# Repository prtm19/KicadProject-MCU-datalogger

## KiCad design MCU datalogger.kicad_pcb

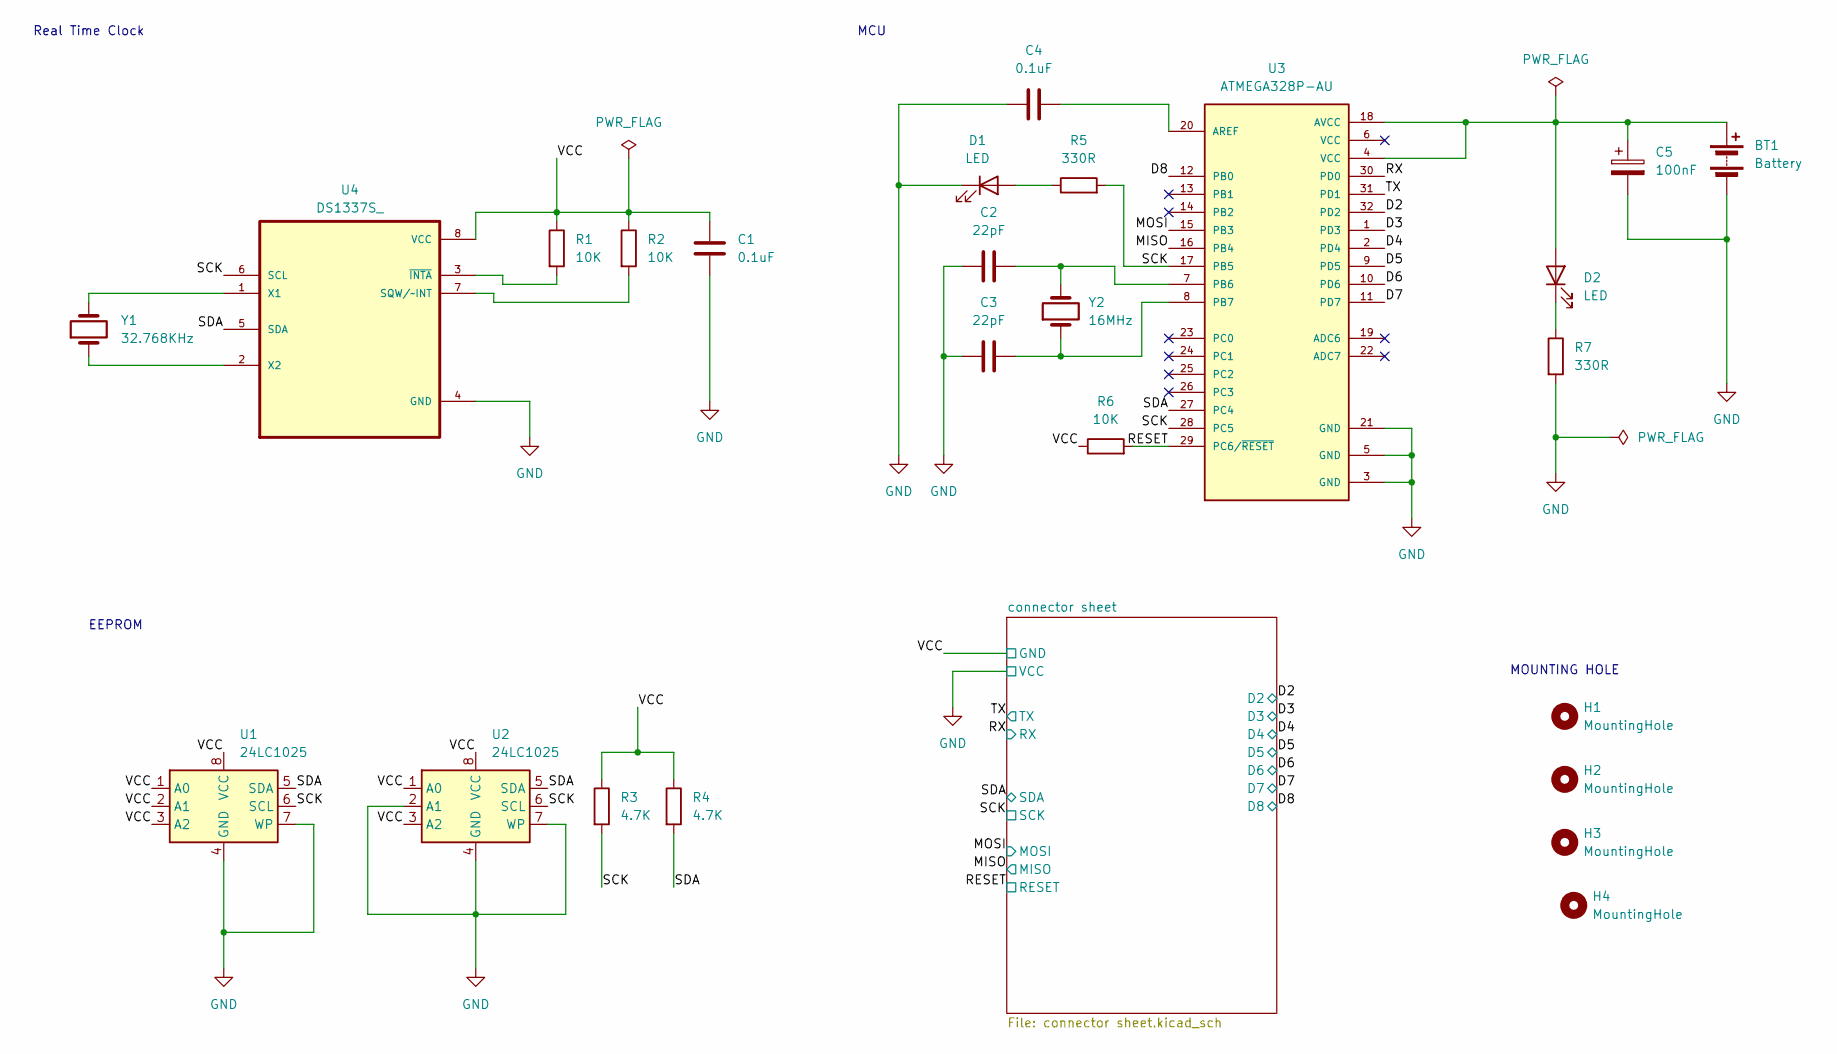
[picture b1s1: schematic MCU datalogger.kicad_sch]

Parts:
BT1: Battery; PinHeader_1x02_P2.54mm_Horizontal
C1, C4: 0.1uF; C_0805_2012Metric
C2, C3: 22pF; C_0805_2012Metric
C5: 100nF; C_0805_2012Metric
D1, D2: LED; LED_0805_2012Metric
H1, H2, H3, H4: MountingHole; MountingHole_2.1mm
R1, R2, R6: 10K; R_0805_2012Metric_Pad1.20x1.40mm_HandSolder
R3, R4: 4.7K; R_0805_2012Metric_Pad1.20x1.40mm_HandSolder
R5, R7: 330R; R_0805_2012Metric_Pad1.20x1.40mm_HandSolder
U1, U2: 24LC1025; SOIC-8_5.3x5.3mm_P1.27mm
U3: ATMEGA328P-AU; QFP80P900X900X120-32N; PARTREV 8271A
U4: DS1337S_; SOIC127P600X175-8N
Y1: 32.768KHz; Crystal_SMD_5032-2Pin_5.0x3.2mm_HandSoldering
Y2: 16MHz; Crystal_SMD_5032-2Pin_5.0x3.2mm_HandSoldering

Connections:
/D2: U3.32 (PD2); also elsewhere on the board
/D3: U3.1 (PD3); also elsewhere on the board
/D4: U3.2 (PD4); also elsewhere on the board
/D5: U3.9 (PD5); also elsewhere on the board
/D6: U3.10 (PD6); also elsewhere on the board
/D7: U3.11 (PD7); also elsewhere on the board
/D8: U3.12 (PB0); also elsewhere on the board
/MISO: U3.16 (PB4); also elsewhere on the board
/MOSI: U3.15 (PB3); also elsewhere on the board
/RESET: R6.2, U3.29 (PC6/~RESET); also elsewhere on the board
/RX: U3.30 (PD0); also elsewhere on the board
/SCK: R3.2, R5.2, U1.6 (SCL), U2.6 (SCL), U3.17 (PB5), U3.28 (PC5), U4.6 (SCL); also elsewhere on the board
/SDA: R4.2, U1.5 (SDA), U2.5 (SDA), U3.27 (PC4), U4.5 (SDA); also elsewhere on the board
/TX: U3.31 (PD1); also elsewhere on the board
/VCC: C1.1, R1.1, R2.1, R3.1, R4.1, R6.1, U1.1 (A0), U1.2 (A1), U1.3 (A2), U1.8 (VCC), U2.1 (A0), U2.3 (A2), U2.8 (VCC), U4.8 (VCC); also elsewhere on the board
GND: BT1.2 (-), C1.2, C2.1, C3.1, C4.2, C5.2, D1.1 (K), R7.2, U1.4 (GND), U1.7 (WP), U2.2 (A1), U2.4 (GND), U2.7 (WP), U3.3 (GND), U3.5 (GND), U3.21 (GND), U4.4 (GND); also elsewhere on the board
unnamed: BT1.1 (+), C5.1, D2.2 (A), U3.4 (VCC), U3.18 (AVCC)
unnamed: D1.2 (A), R5.1
unnamed: D2.1 (K), R7.1
unnamed: C4.1, U3.20 (AREF)
unnamed: C2.2, U3.7 (PB6), Y2.2
unnamed: C3.2, U3.8 (PB7), Y2.1
unnamed: R2.2, U4.7 (SQW/~INT)
unnamed: U4.1 (X1), Y1.2
unnamed: U4.2 (X2), Y1.1
unnamed: R1.2, U4.3 (~INTA)

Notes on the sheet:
MCU
Real Time Clock
EEPROM
MOUNTING HOLE

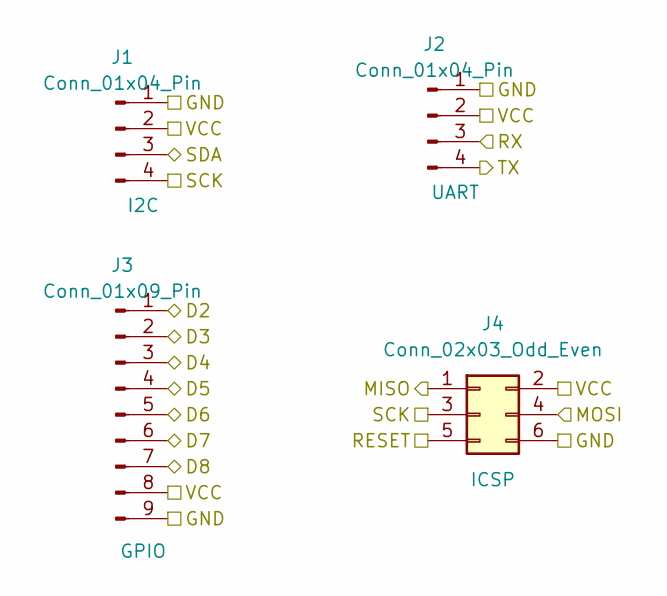
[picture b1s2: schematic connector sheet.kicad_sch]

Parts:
J1, J2: Conn_01x04_Pin; PinHeader_1x04_P2.54mm_Vertical
J3: Conn_01x09_Pin; PinHeader_1x09_P2.54mm_Vertical
J4: Conn_02x03_Odd_Even; PinHeader_2x03_P2.54mm_Vertical

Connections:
/D2: J3.1; also elsewhere on the board
/D3: J3.2; also elsewhere on the board
/D4: J3.3; also elsewhere on the board
/D5: J3.4; also elsewhere on the board
/D6: J3.5; also elsewhere on the board
/D7: J3.6; also elsewhere on the board
/D8: J3.7; also elsewhere on the board
/MISO: J4.1; also elsewhere on the board
/MOSI: J4.4; also elsewhere on the board
/RESET: J4.5; also elsewhere on the board
/RX: J2.3; also elsewhere on the board
/SCK: J1.4, J4.3; also elsewhere on the board
/SDA: J1.3; also elsewhere on the board
/TX: J2.4; also elsewhere on the board
/VCC: J1.1, J2.1, J3.9, J4.6; also elsewhere on the board
GND: J1.2, J2.2, J3.8, J4.2; also elsewhere on the board

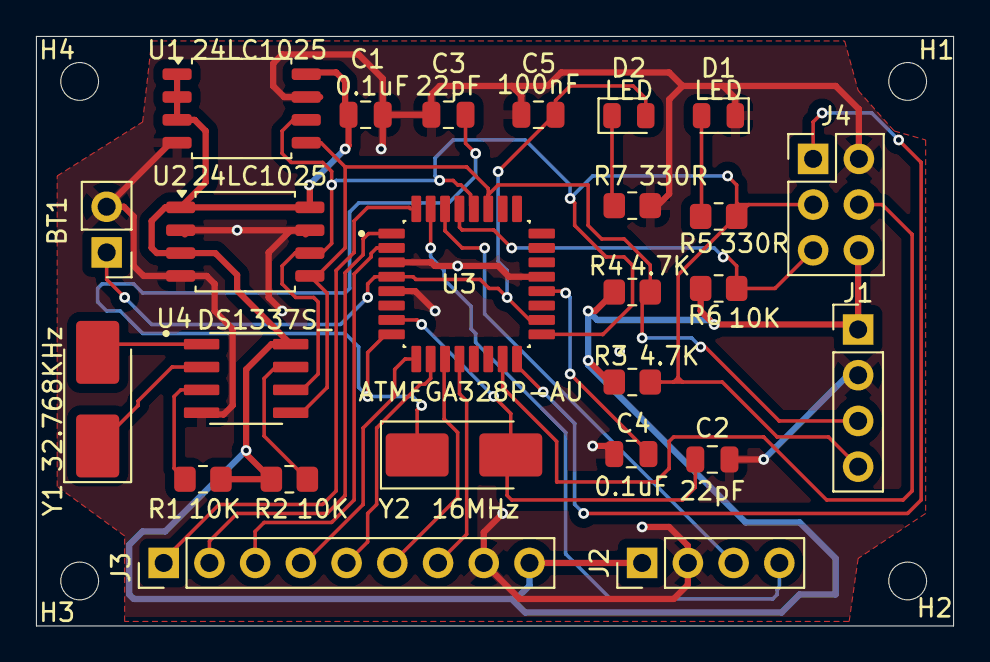
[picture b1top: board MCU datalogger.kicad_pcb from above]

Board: 2 copper layers, 51.0 x 32.8 mm, 29 parts (0 on the bottom side), 26 nets.

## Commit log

2025-09-17 upload file
2025-09-17 add readme file
2025-09-17 2 layer
2025-09-17 4 layer
2025-09-17 update 4layer
2025-09-20 update 2 layer
2025-09-20 update gerber file
2025-10-19 Add copper layer
